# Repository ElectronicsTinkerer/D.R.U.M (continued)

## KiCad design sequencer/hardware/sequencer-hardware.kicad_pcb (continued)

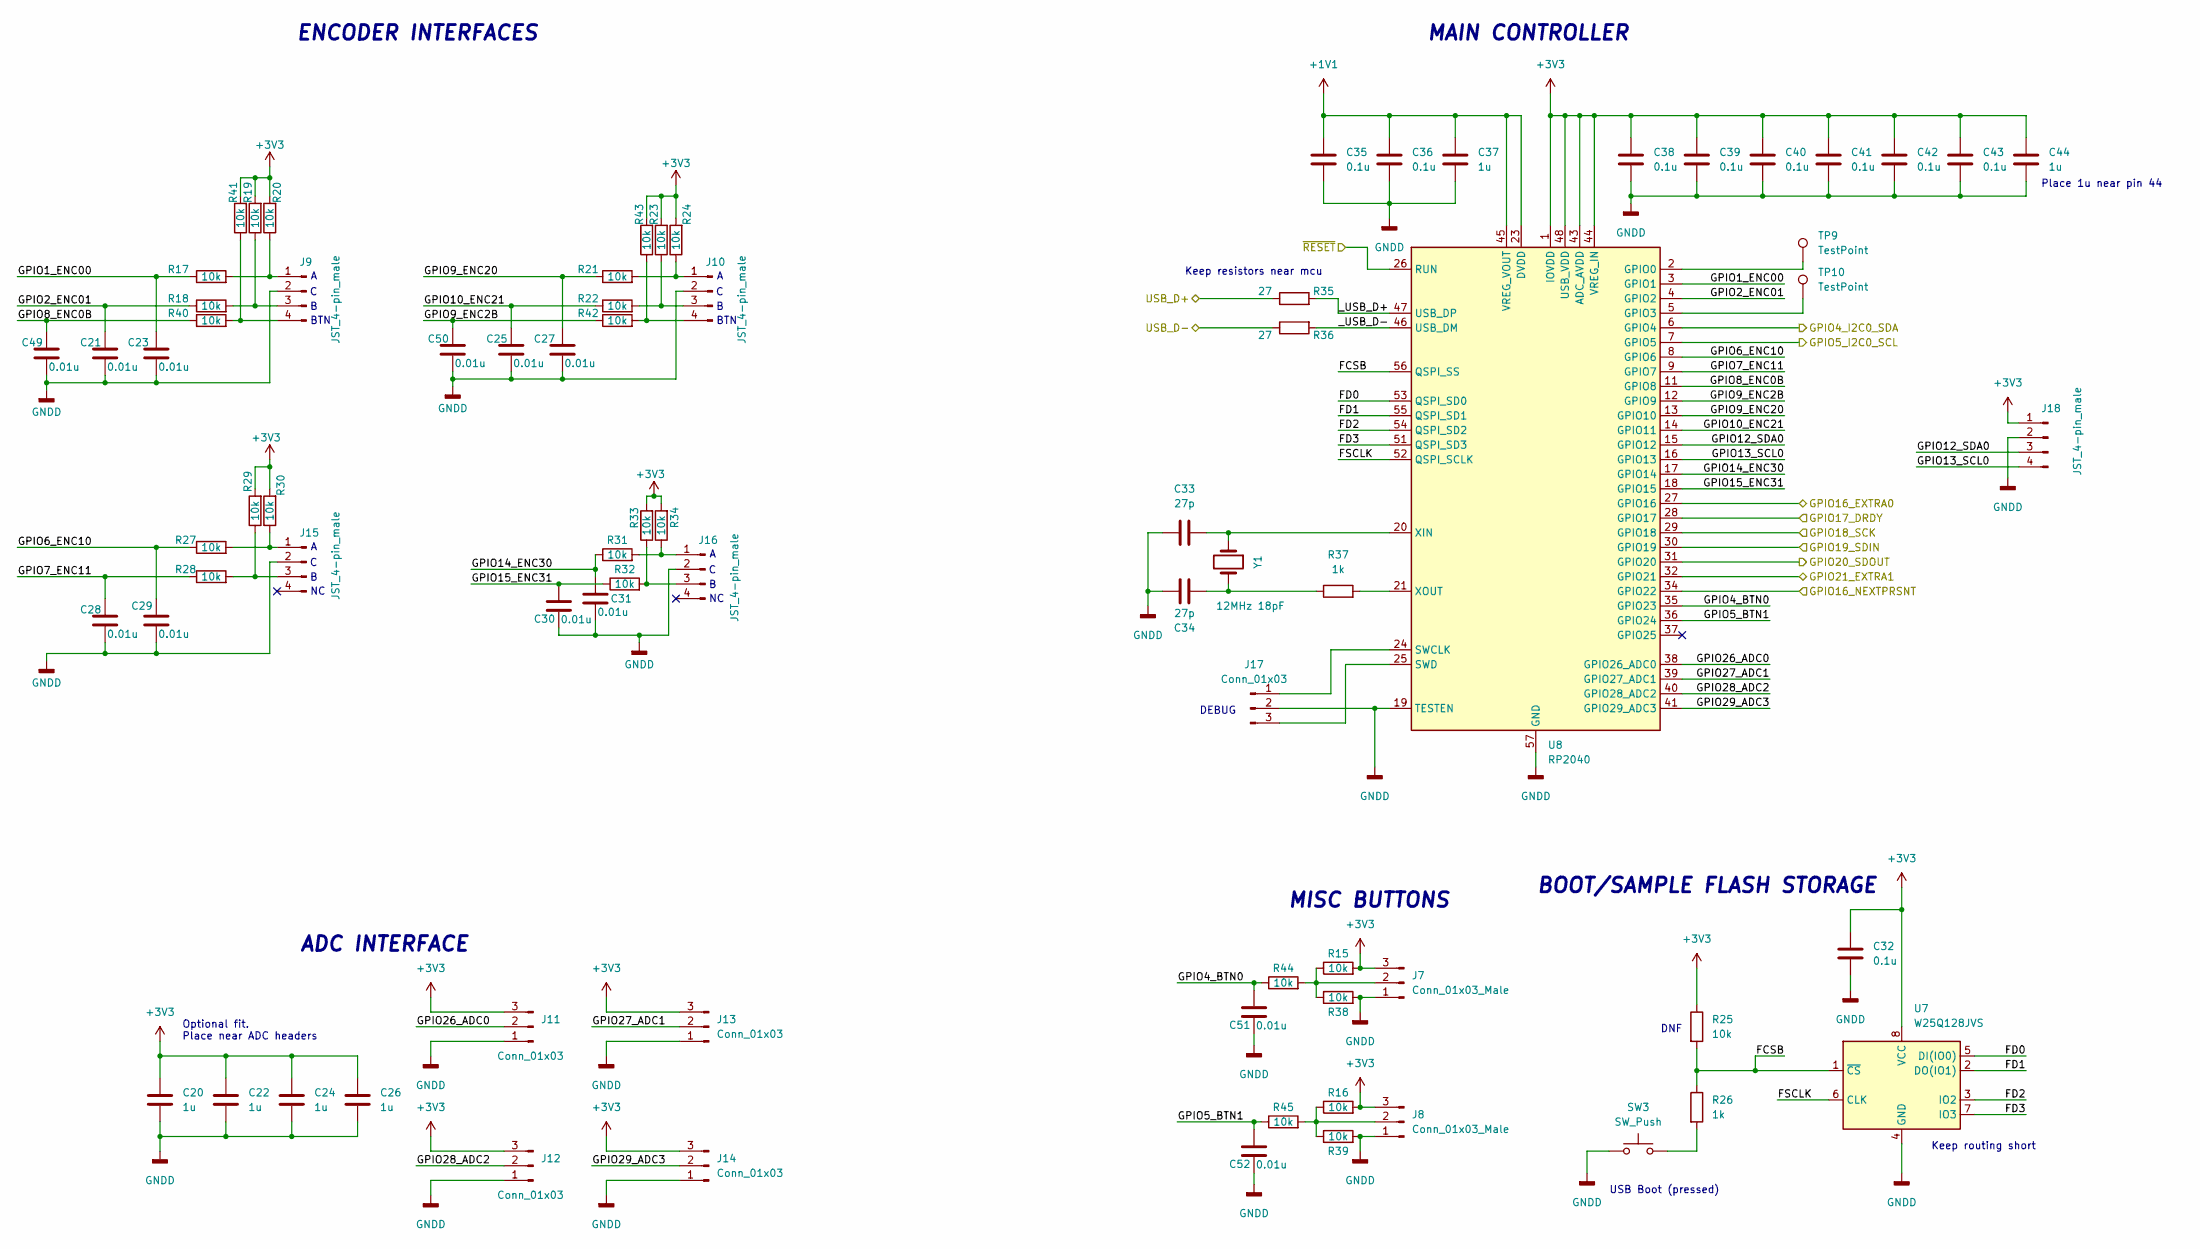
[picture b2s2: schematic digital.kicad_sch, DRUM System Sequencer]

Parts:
C20, C22, C24, C26, C37, C44: 1u; C_0603_1608Metric_Pad1.08x0.95mm_HandSolder
C21, C23, C25, C27, C28, C29, C30, C31, C49, C50, C51, C52: 0.01u; C_0805_2012Metric_Pad1.18x1.45mm_HandSolder
C32, C35, C36, C38, C39, C40, C41, C42, C43: 0.1u; C_0603_1608Metric_Pad1.08x0.95mm_HandSolder
C33, C34: 27p; C_0603_1608Metric_Pad1.08x0.95mm_HandSolder
J7, J8: Conn_01x03_Male; PinHeader_1x03_P2.54mm_Vertical
J9, J10, J15, J16, J18: JST_4-pin_male; JST_PH_B4B-PH-K_1x04_P2.00mm_Vertical
J11, J12, J13, J14, J17: Conn_01x03; PinHeader_1x03_P2.54mm_Vertical
R15, R16, R17, R18, R19, R20, R21, R22, R23, R24, R25, R27, R28, R29, R30, R31, R32, R33, R34, R38, R39, R40, R41, R42, R43, R44, R45: 10k; R_0603_1608Metric_Pad0.98x0.95mm_HandSolder
R26, R37: 1k; R_0603_1608Metric_Pad0.98x0.95mm_HandSolder
R35, R36: 27; R_0603_1608Metric_Pad0.98x0.95mm_HandSolder
SW3: SW_Push; TE_ConnMSLPT5252CG1
TP9, TP10: TestPoint; TestPoint_Pad_D1.5mm
U7: W25Q128JVS; SOIC-8_5.23x5.23mm_P1.27mm
U8: RP2040; QFN-56-1EP_7x7mm_P0.4mm_EP3.2x3.2mm
Y1: 12MHz 18pF; Crystal_SMD_HC49-SD

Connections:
+1V1: C35.1, C36.1, C37.1, U8.23 (DVDD), U8.45 (VREG_VOUT), U8.50 (DVDD)
/CBUS_DRDY: U8.28 (GPIO17); also elsewhere on the board
/CBUS_EXTRA0: U8.27 (GPIO16); also elsewhere on the board
/CBUS_EXTRA1: U8.32 (GPIO21); also elsewhere on the board
/CBUS_NEXTPRSNT: U8.34 (GPIO22); also elsewhere on the board
/CBUS_SCK: U8.29 (GPIO18); also elsewhere on the board
/CBUS_SDOUT: U8.31 (GPIO20); also elsewhere on the board
/CBUS_SDRETIN: U8.30 (GPIO19); also elsewhere on the board
/D.R.U.M. Sequencer Digital/FCSB: R25.2, R26.1, U7.1 (~CS), U8.56 (QSPI_SS)
/D.R.U.M. Sequencer Digital/FD0: U7.5 (DI(IO0)), U8.53 (QSPI_SD0)
/D.R.U.M. Sequencer Digital/FD1: U7.2 (DO(IO1)), U8.55 (QSPI_SD1)
/D.R.U.M. Sequencer Digital/FD2: U7.3 (IO2), U8.54 (QSPI_SD2)
/D.R.U.M. Sequencer Digital/FD3: U7.7 (IO3), U8.51 (QSPI_SD3)
/D.R.U.M. Sequencer Digital/FSCLK: U7.6 (CLK), U8.52 (QSPI_SCLK)
/D.R.U.M. Sequencer Digital/GPIO1_ENC00: C23.1, R17.1, U8.3 (GPIO1)
/D.R.U.M. Sequencer Digital/GPIO2_ENC01: C21.1, R18.1, U8.4 (GPIO2)
/D.R.U.M. Sequencer Digital/GPIO4_BTN0: C51.1, R44.1, U8.35 (GPIO23)
/D.R.U.M. Sequencer Digital/GPIO5_BTN1: C52.1, R45.1, U8.36 (GPIO24)
/D.R.U.M. Sequencer Digital/GPIO6_ENC10: C29.1, R27.1, U8.8 (GPIO6)
/D.R.U.M. Sequencer Digital/GPIO7_ENC11: C28.1, R28.1, U8.9 (GPIO7)
/D.R.U.M. Sequencer Digital/GPIO8_ENC0B: C49.1, R40.1, U8.11 (GPIO8)
/D.R.U.M. Sequencer Digital/GPIO9_ENC2B: C50.1, R42.1, U8.12 (GPIO9)
/D.R.U.M. Sequencer Digital/GPIO9_ENC20: C27.1, R21.1, U8.13 (GPIO10)
/D.R.U.M. Sequencer Digital/GPIO10_ENC21: C25.1, R22.1, U8.14 (GPIO11)
/D.R.U.M. Sequencer Digital/GPIO12_SDA0: J18.3, U8.15 (GPIO12)
/D.R.U.M. Sequencer Digital/GPIO13_SCL0: J18.4, U8.16 (GPIO13)
/D.R.U.M. Sequencer Digital/GPIO14_ENC30: C31.1, R31.1, U8.17 (GPIO14)
/D.R.U.M. Sequencer Digital/GPIO15_ENC31: C30.1, R32.1, U8.18 (GPIO15)
/D.R.U.M. Sequencer Digital/GPIO26_ADC0: J11.2, U8.38 (GPIO26_ADC0)
/D.R.U.M. Sequencer Digital/GPIO27_ADC1: J13.2, U8.39 (GPIO27_ADC1)
/D.R.U.M. Sequencer Digital/GPIO28_ADC2: J12.2, U8.40 (GPIO28_ADC2)
/D.R.U.M. Sequencer Digital/GPIO29_ADC3: J14.2, U8.41 (GPIO29_ADC3)
/D.R.U.M. Sequencer Digital/_USB_D+: R35.2, U8.47 (USB_DP)
/D.R.U.M. Sequencer Digital/_USB_D-: R36.2, U8.46 (USB_DM)
/KEY_SCL: U8.7 (GPIO5); also elsewhere on the board
/KEY_SDA: U8.6 (GPIO4); also elsewhere on the board
/RUN: U8.26 (RUN); also elsewhere on the board
/USB_D+: R35.1; also elsewhere on the board
/USB_D-: R36.1; also elsewhere on the board
GNDD: C20.2, C21.2, C22.2, C23.2, C24.2, C25.2, C26.2, C27.2, C28.2, C29.2, C30.2, C31.2, C32.2, C33.1, C34.2, C35.2, C36.2, C37.2, C38.2, C39.2, C40.2, C41.2, C42.2, C43.2, C44.2, C49.2, C50.2, C51.2, C52.2, J7.1, J8.1, J9.2, J10.2, J11.1, J12.1, J13.1, J14.1, J15.2, J16.2, J17.2, J18.2, R38.2, R39.2, SW3.1, U7.4 (GND), U8.19 (TESTEN), U8.57 (GND); also elsewhere on the board
unnamed: C33.2, U8.20 (XIN), Y1.1
unnamed: C34.1, R37.1, Y1.2
unnamed: J7.2, R15.1, R38.1, R44.2
unnamed: J8.2, R16.1, R39.1, R45.2
unnamed: J9.1, R17.2, R20.1
unnamed: J9.3, R18.2, R19.1
unnamed: J9.4, R40.2, R41.1
unnamed: J10.1, R21.2, R24.1
unnamed: J10.3, R22.2, R23.1
unnamed: J10.4, R42.2, R43.1
unnamed: J15.1, R27.2, R30.1
unnamed: J15.3, R28.2, R29.1
unnamed: J16.1, R31.2, R34.1
unnamed: J16.3, R32.2, R33.1
unnamed: J17.1, U8.24 (SWCLK)
unnamed: J17.3, U8.25 (SWD)
unnamed: R26.2, SW3.2
unnamed: R37.2, U8.21 (XOUT)
unnamed: TP9.1, U8.2 (GPIO0)
unnamed: TP10.1, U8.5 (GPIO3)

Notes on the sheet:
ENCODER INTERFACES
DEBUG
ADC INTERFACE
MAIN CONTROLLER
BTN
DNF
Optional fit. Place near ADC headers
Place 1u near pin 44
BOOT/SAMPLE FLASH STORAGE
MISC BUTTONS
Keep resistors near mcu
USB Boot (pressed)
Keep routing short

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
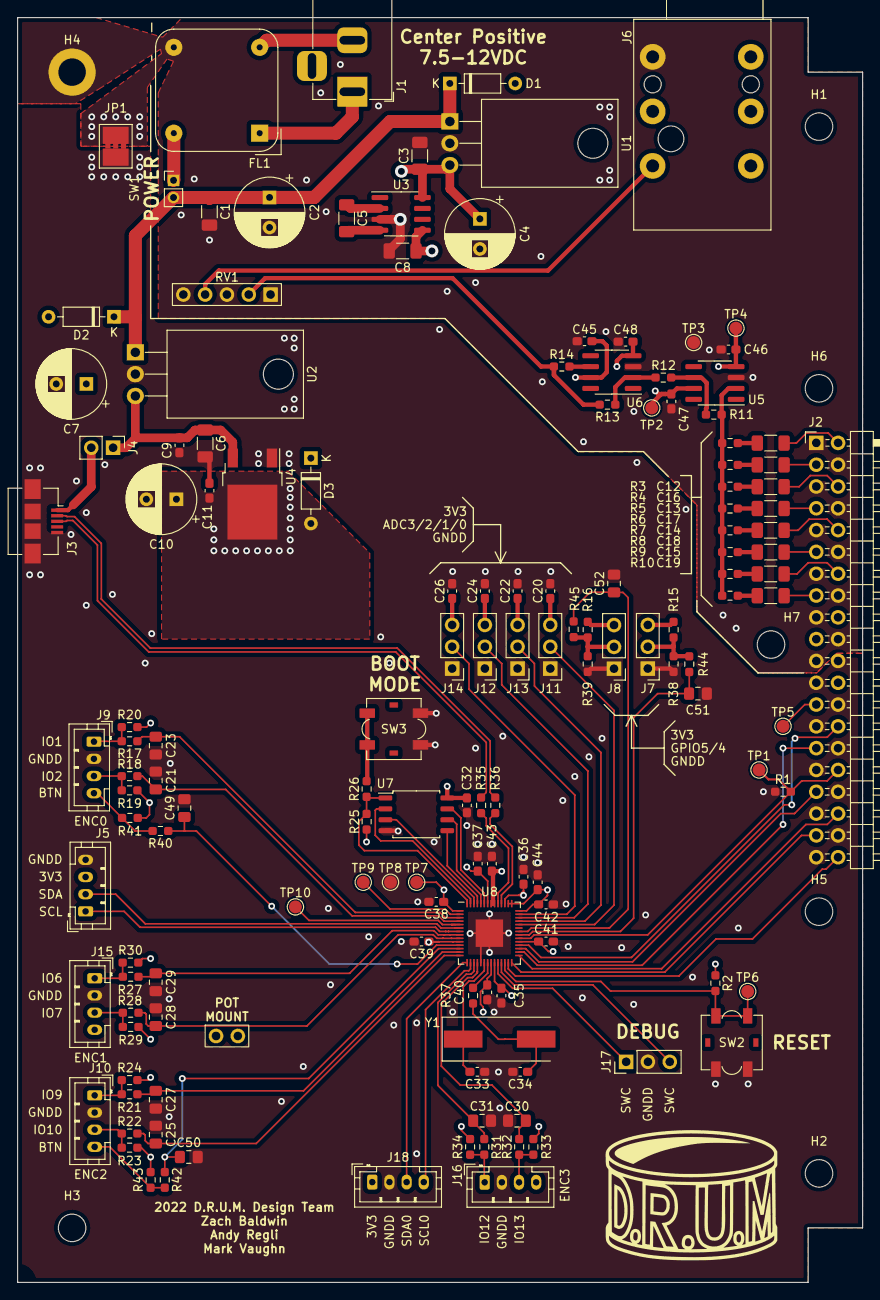
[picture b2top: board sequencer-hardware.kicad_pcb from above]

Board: 4 copper layers, 98.4 x 147.3 mm, 150 parts (0 on the bottom side), 94 nets.

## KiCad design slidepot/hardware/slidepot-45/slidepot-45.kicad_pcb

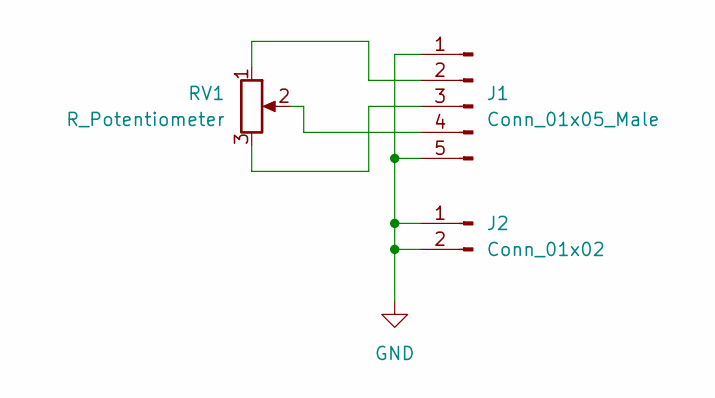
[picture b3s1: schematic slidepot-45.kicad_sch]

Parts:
J1: Conn_01x05_Male; PinHeader_1x05_P2.54mm_Vertical
J2: Conn_01x02; PinHeader_1x02_P2.54mm_Vertical
RV1: R_Potentiometer; Potentiometer_Bourns_PTA4543_Single_Slide

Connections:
GND: J1.1, J1.5, J2.1, J2.2
unnamed: J1.2, RV1.1
unnamed: J1.3, RV1.3
unnamed: J1.4, RV1.2

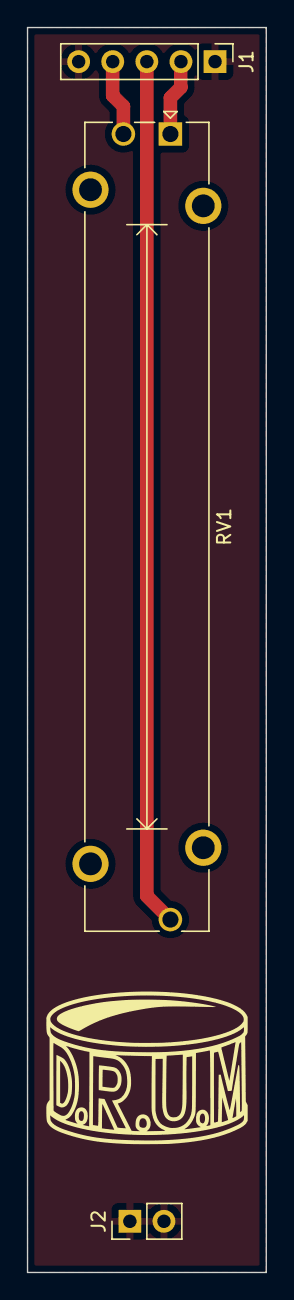
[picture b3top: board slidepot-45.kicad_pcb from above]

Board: 2 copper layers, 17.8 x 92.7 mm, 3 parts (0 on the bottom side), 4 nets.

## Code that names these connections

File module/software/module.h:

/**
 * MODULE CONTROLLER
 * 
 * Authors:
 * Zach Baldwin
 * Andy Regli
 * Mark Vaughn
 *
 */


#ifndef DRUM_MODULE_H
#define DRUM_MODULE_H

// Pin definitions
// GPIO 0
#define GPIO_ENC0        1
#define GPIO_ENC1        2
#define GPIO_ENC2        3
// GPIO 4
// GPIO 5
#define GPIO_CBUS_EXTRA1 6
#define GPIO_CBUS_EXTRA0 7
#define GPIO_CBUS_SDIN   8
#define GPIO_CBUS_DRDY   9
#define GPIO_CBUS_SCK    10
#define GPIO_CBUS_SDOUT  11
#define GPIO_TP7         12
#define GPIO_TP8         13
#define GPIO_TP9         14
// GPIO 15
#define GPIO_DAC_LDACB   16
#define GPIO_DAC_CSB     17
#define GPIO_DAC_SCK     18
#define GPIO_DAC_SDAT    19
#define GPIO_CHAN_FULL   20
// GPIO 21
// GPIO 22
#define GPIO_BTN0        23
#define GPIO_BTN1        24
// GPIO 25
#define GPIO_ADC0        26
#define GPIO_ADC1        27
#define GPIO_ADC2        28
#define GPIO_ADC3        29

// Named pin mappings
#define MOD_TEMPO_SYNC   GPIO_CBUS_EXTRA1
#define MOD_STAT_IRQ     GPIO_CBUS_EXTRA0
#define GPIO_SEL_BTN     GPIO_BTN0
#define GPIO_SEL_LED     GPIO_ENC0

#define SPI_DAC_DATA_RATE_HZ 10000000
#define AUDIO_SAMPLE_RATE_HZ 44100

#define ALARM_TEMPO_SAMPLE_US 75

#define VARIABILITY_STEPS 4 // MUST be a power of 2!
#define VARIABILITY_STEPS_LOG 2 // LOG2(VARIABILITY_STEPS)

typedef struct beat_data {
    signed int ubeat    : 4;
    unsigned int veloc  : 4; // 0 = no hit
    unsigned int sample : 4;
} beat_data_t;

void clear_beats(void);
uint16_t read_variability_pot(void);
void send_sample_to_dac(void);
void write_dac(uint16_t);
void isr_gpio_handler(unsigned int, uint32_t);
void isr_mod_sel_btn(unsigned int, uint32_t);
int64_t alarm_mod_stat_callback(alarm_id_t, void *);
void set_mod_stat_line(bool);
void isr_tempo_sync(unsigned int, uint32_t);
int64_t alarm_mod_beat_callback(alarm_id_t, void *);
bool isr_sample(repeating_timer_t *);
void intermodule_command_handler(void);
void execute_intermodule_command(ctlword_t);

#endif

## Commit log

2022-09-14 Improved description!
2022-09-14 Init dir structure; create kicad projects
2022-09-15 Add LDO & QSPI flash to module schematic
2022-09-18 Designed a rough audio summing bus
2022-09-18 A few more edits
2022-09-19 Add USB, XTAL, ADC headers, MCU bypass caps, reset
2022-09-19 Added master volume
    For next time: need to consider level shifting on the DAC output
    0-3.3V -> 0-12V?
2022-09-19 Add DAC connections
2022-09-19 Start work on dsub pinout/connections
2022-09-21 Add module schematic TODO
2022-09-21 Reworked audio summing in main sequencer.
    Might still need to think about level shifting
2022-09-21 Added analog mux to custom symbol library
2022-09-21 Isolated Analog & Digital GND
    Also added coupling caps to sequencer mixer
2022-09-21 Reworked audio routing to avoid MUX
2022-09-23 Move digital to separate sheet
2022-09-23 Add loopback routing mux; add digital signals to headers
2022-09-24 Added pull-down resistors to analog passthroughs
2022-09-25 Finished preliminary audio routing
2022-09-25 Fixed a few weird wires
2022-09-26 Add ADC vref, encoder & button headers
2022-09-26 Add datasheet links for OPA340 and MAX6070
2022-09-26 Fix voltage rev supply (5V -> 3V3)
2022-09-26 Add most footprints
2022-09-26 Finish footprint assignments; create cusom footprint lib
2022-09-26 Fix header footprints
2022-09-26 Begin layout process for module
2022-09-27 Complete board layout component placement & outline approx
2022-09-27 Begin digital side routing
2022-09-28 Ground plane
2022-09-28 transferred digital system to sequencer schematic
2022-09-28 Route/move USB
2022-09-28 Reorder RP2040 GPIO lines for improved routability
2022-09-28 Route global SPI bus
2022-09-30 Created slidepot daughter board
2022-09-30 Replace slidepot with slidepot daughterboard
2022-09-30 Correct direction of input/output connectors for digital signals
2022-10-01 Module Analog preliminaty routing complete
2022-10-03 Create Solidworks file
2022-10-03 Export STEP of module
2022-10-03 Finish Module PCB routing (DAC SPI lines)
2022-10-03 Fix +5V plane, cleanup silkscreen
2022-10-03 Finish Sequencer Schematic
2022-10-05 Update sequencer schematic
2022-10-07 John Gibbons 30Khz LP & DAC analog power jumper
2022-10-07 Generate STEP of Module
2022-10-07 Implement changes to sequencer recommended by John
2022-10-10 Denote start ground point
2022-10-10 Add pull down button resistor option
2022-10-11 Add M3 mounting holes; add HW/Layout REV IDs
2022-10-11 Add DRUM logo
2022-10-11 Modify main enclosure to better fit connectors
2022-10-12 Fix scan chain pin labeling on input connector
2022-10-12 Update solidworks assy
2022-10-14 Move Module CAD into cad folder
2022-10-15 Finalized PCB soldermask labeling for Module
2022-10-15 Update Solidworks files
2022-10-15 Add optional pulldown resistors to buttons
2022-10-15 change routing
2022-10-15 Adjust Library Structure
2022-10-15 Add filter sections to encoders
2022-10-17 Disconnect GNDD from GNDA to prevent routing confusion
2022-10-17 Do a lot of random stuff
2022-10-18 Add project copy of RP2040 footprint
2022-10-19 more library weirdness
2022-10-21 Split slidepot into 45 and 60 mm boards
2022-10-21 Add common mode choke
2022-10-21 Rename slidepot 45 and 60
2022-10-21 Update slideot-45 footprint
2022-10-21 Update sequencer-hardware.kicad_sch
    footprints updated
2022-10-21 more footprints
2022-10-21 some routing added
2022-10-21 More routing
2022-10-21 Adjust component placement
2022-10-22 add mounting holes, arrange all parts
2022-10-25 Add ground planes
2022-10-25 Route analog domain
2022-10-25 Route digital domain
2022-10-25 Cleanup silkscreen
2022-10-25 Assign part numbers
2022-10-25 Add star ground point
2022-10-26 Add testpoints
2022-10-26 Add final mounting hole and generate STEP file
2022-10-27 Move JP1 text
2022-10-27 Add OLED header
2022-10-27 Increase size of layer 3 planes
2022-10-27 Resize sequencer PCB
2022-10-28 remove stupid tabs
2022-10-28 Add board notches; align mounting holes
2022-10-28 move 40-pin connector
2022-10-28 Add test points; update silkscreen
2022-10-28 Implement star grounding
2022-10-30 Fix OPA power polarity; Add Reg protection diodes; Cleanup silk
2022-10-30 Export Gerbers
2022-10-31 Generate slidepot gerbers
2022-11-02 Export slidepot gerbers; start module software
2022-11-04 Attempt to use FreeCAD
2022-11-04 Set up CMAKE
2022-11-06 Create function signatures for sequencer
2022-11-06 Fix sequencer naming
2022-11-06 Add function signatures for module
2022-11-09 modify module enclosure, fix 3d model references
2022-11-09 Add GPIO interrupt setup
2022-11-11 CAD Cleanup
2022-11-11 Test timer interrupts; Copy in OLED test code
2022-11-11 It's python time!
2022-11-13 Enclosure UI mega update
2022-11-13 Complete Enclosure
2022-11-14 Start porting of C to Python
2022-11-14 Clone Adafruit Seesaw library for NeoTrellis
2022-11-15 Write the Wire.h library
2022-11-15 NeoTrellis now builds...
2022-11-15 The timer now works in C
2022-11-15 Resolve lots of syntax errors in Wire.h; now there's linking errors...
2022-11-15 It compiles again
2022-11-15 Add I2c Init; Fix minor errors inWire; IT WORKS!!! (Mostly, there's one Neopixel stuck on)
2022-11-15 Fix 'stuck pixel'; Increase Request Timeout
2022-11-15 Add 'beat' display on pads
2022-11-15 Remove PY file
2022-11-16 OLED displays splash (Fix SSD1306 libs)
2022-11-16 Add tempo encoder adjustment and tempo display
2022-11-16 Improve time signature storage
2022-11-16 Add play/pause button code
2022-11-17 Add button debounce passives
2022-11-17 Route button debounce passives; bump HW rev to 1.1
2022-11-17 Route button debounce passives; bump HW rev to 1.1 (repeat)
2022-11-17 Add EXTRA1, btn debounce passives; Bump HW rev to 1.1
2022-11-17 Create short 45mm slidepot
2022-11-18 Add time signature display
2022-11-18 Bump I2C frequency to 400kHz; correct play/pause timer operation
2022-11-21 Revise CAD, add power switch
2022-11-29 Update pin nums for REV1.1 board; add tsig adjustment
2022-11-30 Add rev1.2 ideas file
2022-11-30 Begin sequencer PIO Tx/Rx work
2022-12-01 Add init for Rx and Tx PIO blocks on sequencer
2022-12-02 Add core1 beat updates; allow setting of beats via buttons
2022-12-02 Add velocity OLED readout
2022-12-03 PIO TX for sequencer functional
2022-12-03 RX PIO FIFO recieves correct data!
2022-12-03 Start module code; add select button ISR
2022-12-03 Modify tx to lower clk after drdy rises
2022-12-03 Module successfully loops back SIO data
2022-12-03 Implement determine connected module count
2022-12-04 Fix connected module count function
2022-12-04 Change splash to DRUM logo
2022-12-04 Add intermodule command handler
2022-12-04 Make mutex names consistent
2022-12-04 FIX: DRDY now goes high prior to SCK
2022-12-04 Fix module count function
2022-12-04 Fix pull noblock bug... The (terrible) solution was to add an ifempty to the pull at the beginning of the transmission. For some reason, `pull noblock` blocks unless it is preceded by a `mov ISR, OSR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
2022-12-05 Clear command buffer before performing read shift
2022-12-05 Add beat 'modified' message sending
2022-12-05 Implement DAC driver & ISR
2022-12-05 Implement preliminary tempo sync
2022-12-05 Add samples & sample to C array converter
2022-12-05 Remove 'sample' beat field; Velocity playback fix Also: * It plays noises! (Drum samples, to be precise!!!)
2022-12-05 Beat 0 synchronization implemented
2022-12-06 Add serbus docs
2022-12-06 Fix spelling in serbus docs & update timing diagram
2022-12-06 Implement variability
2022-12-06 Add debug 1kHz sine wave mode
2022-12-06 Scan operational
2022-12-06 Fix intermodule bus (bidirectional comm now working\!)
2022-12-06 Module (de)sel implemented
2022-12-06 Change serbus SVG->PNG
2022-12-07 Add color representation of velocity on grid
2022-12-07 Start system architecture docs
2022-12-07 Add docs about basic usage; UI diagram breakouts
2022-12-07 Change clear button to use timeout
2022-12-07 Update interface diagram; Start IPC docs
2022-12-07 Fix path of CAD rendering
2022-12-07 Correct variability randomization
2022-12-07 Add module interface diagram
2022-12-07 Fix type on module interface diagram
2022-12-08 Add finalized assembly and PCB photos
2022-12-08 Fix beat variability
2022-12-08 Fix 1kHz debug rate
2022-12-11 Add 'scope capture of serbus discovery phase
2022-12-12 Update IPC docs; add samples docs
2022-12-12 Resore deleted ipc diagram
